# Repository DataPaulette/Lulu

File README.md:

Lulu
=========

Lulu is an e-textile PCB for optical fibers light injection

# Fusion Premium PCB
 - Quantity : 12 PCB - 60mm by 60mm. Each PCB contain 20 panelized PCB ( array 5 x 4 ) v-cut
 - Gerbers : files attached
 - Price : 240$

# Parameters :
 - Lulu size : 12.45mm * 12.45mm
 - Layer : 2
 - Thickness : 0.6 mm
 - Copper weight : 2 oz
 - Colour : Black
 - Silkscreen : White
 - Finish : Hasl
 - E-testing : No
 - Shipping : Normal lead time

# Part list
 - Lulu PCB  - http://www.seeedstudio.com/ ($1.33 / pièce)
 - LED OSRAM 350mA - http://aliexpress.com ($0.65 / pièce)
 - Brass tube 2 MM Hole X 10 MM Length - http://ebay.com  ($0.05 / pièce)
 - JTE-1.5 en 8mm (http://www.jonction-et-derivation-electriques.fr) ($0.02 / pièce)
 - 35 optical fibres diameter 0.25mm ($ TODO)

# TODO
 - add onboard small microcontroleur to allow bus addressing light control like the WS2812 LEDs ;-)
 - https://github.com/ytai/pixie

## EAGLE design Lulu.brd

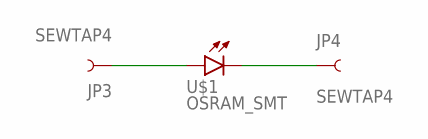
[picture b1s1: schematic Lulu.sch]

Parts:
JP3, JP4: SEWTAP4; PETAL-SMALL
U$1: OSRAM_SMT; OSLON

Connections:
unnamed: JP3.1, U$1.A
unnamed: JP4.1, U$1.C

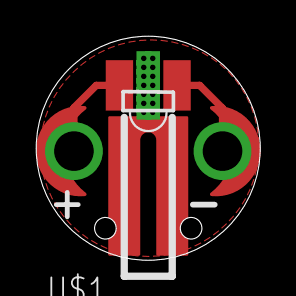
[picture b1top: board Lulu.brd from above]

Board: 2 copper layers, 12.4 x 12.4 mm, 3 parts (0 on the bottom side), 2 nets.

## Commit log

2015-08-19 Initial comit
2015-08-19 Clean UP
2015-08-19 small correction
2015-08-26 Ahdded PCB Parameters
2016-09-15 add panelyzed gerber ;-)

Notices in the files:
parts and their libraries:
LilyPad-Wearables: Licensing:Creative Commons ShareAlike 4.0 International - https://creativecommons.org/licenses/by-sa/4.0
